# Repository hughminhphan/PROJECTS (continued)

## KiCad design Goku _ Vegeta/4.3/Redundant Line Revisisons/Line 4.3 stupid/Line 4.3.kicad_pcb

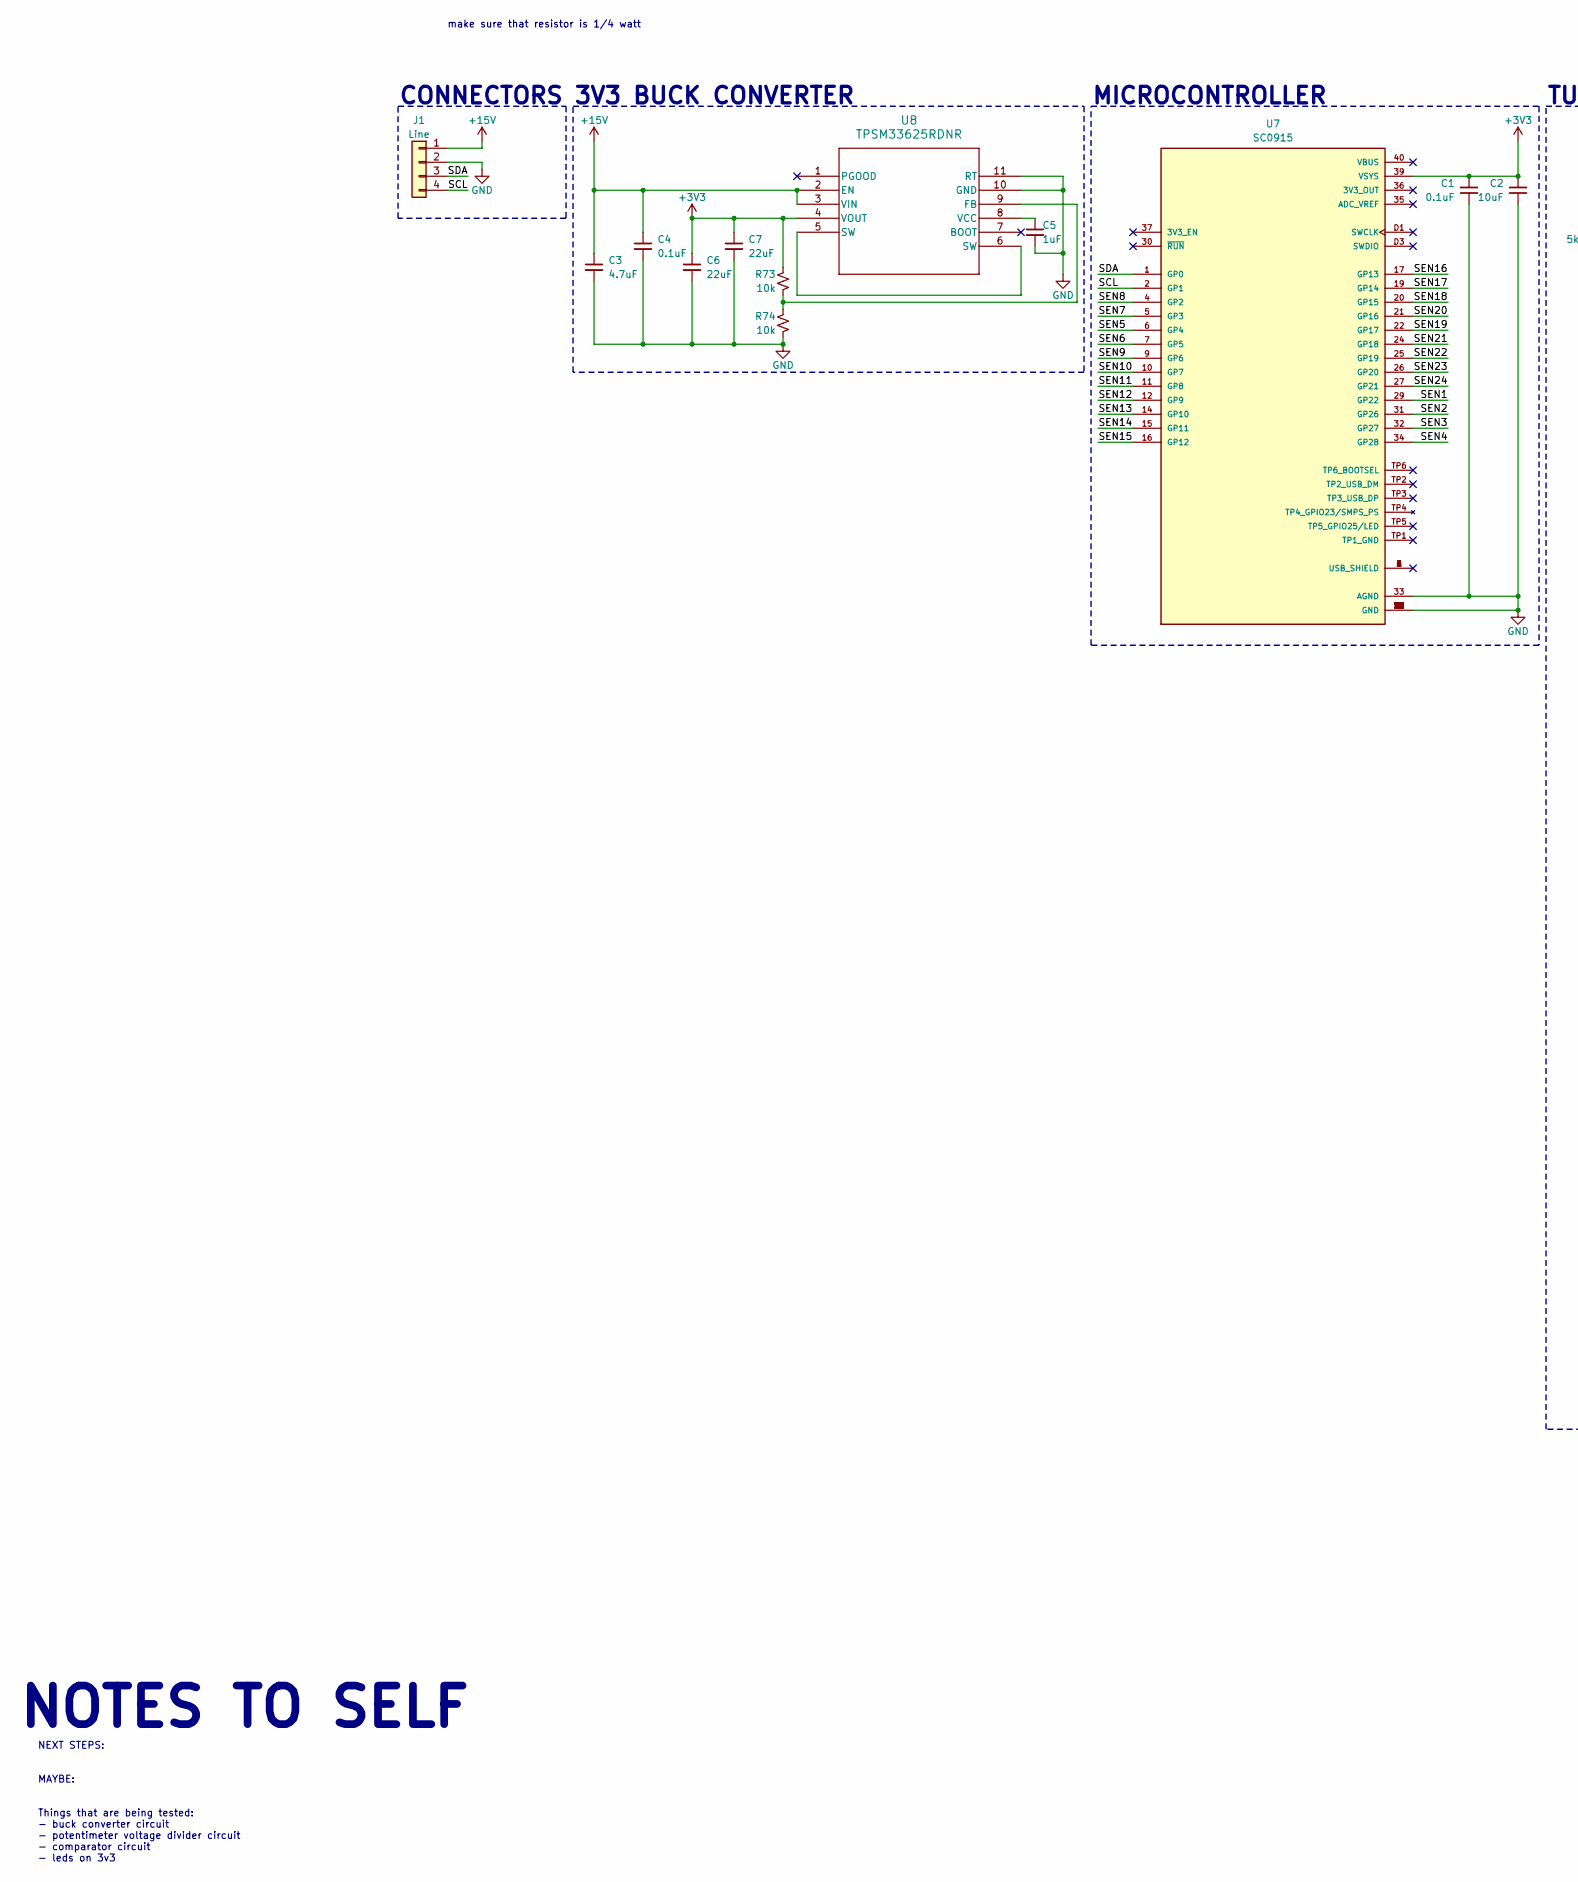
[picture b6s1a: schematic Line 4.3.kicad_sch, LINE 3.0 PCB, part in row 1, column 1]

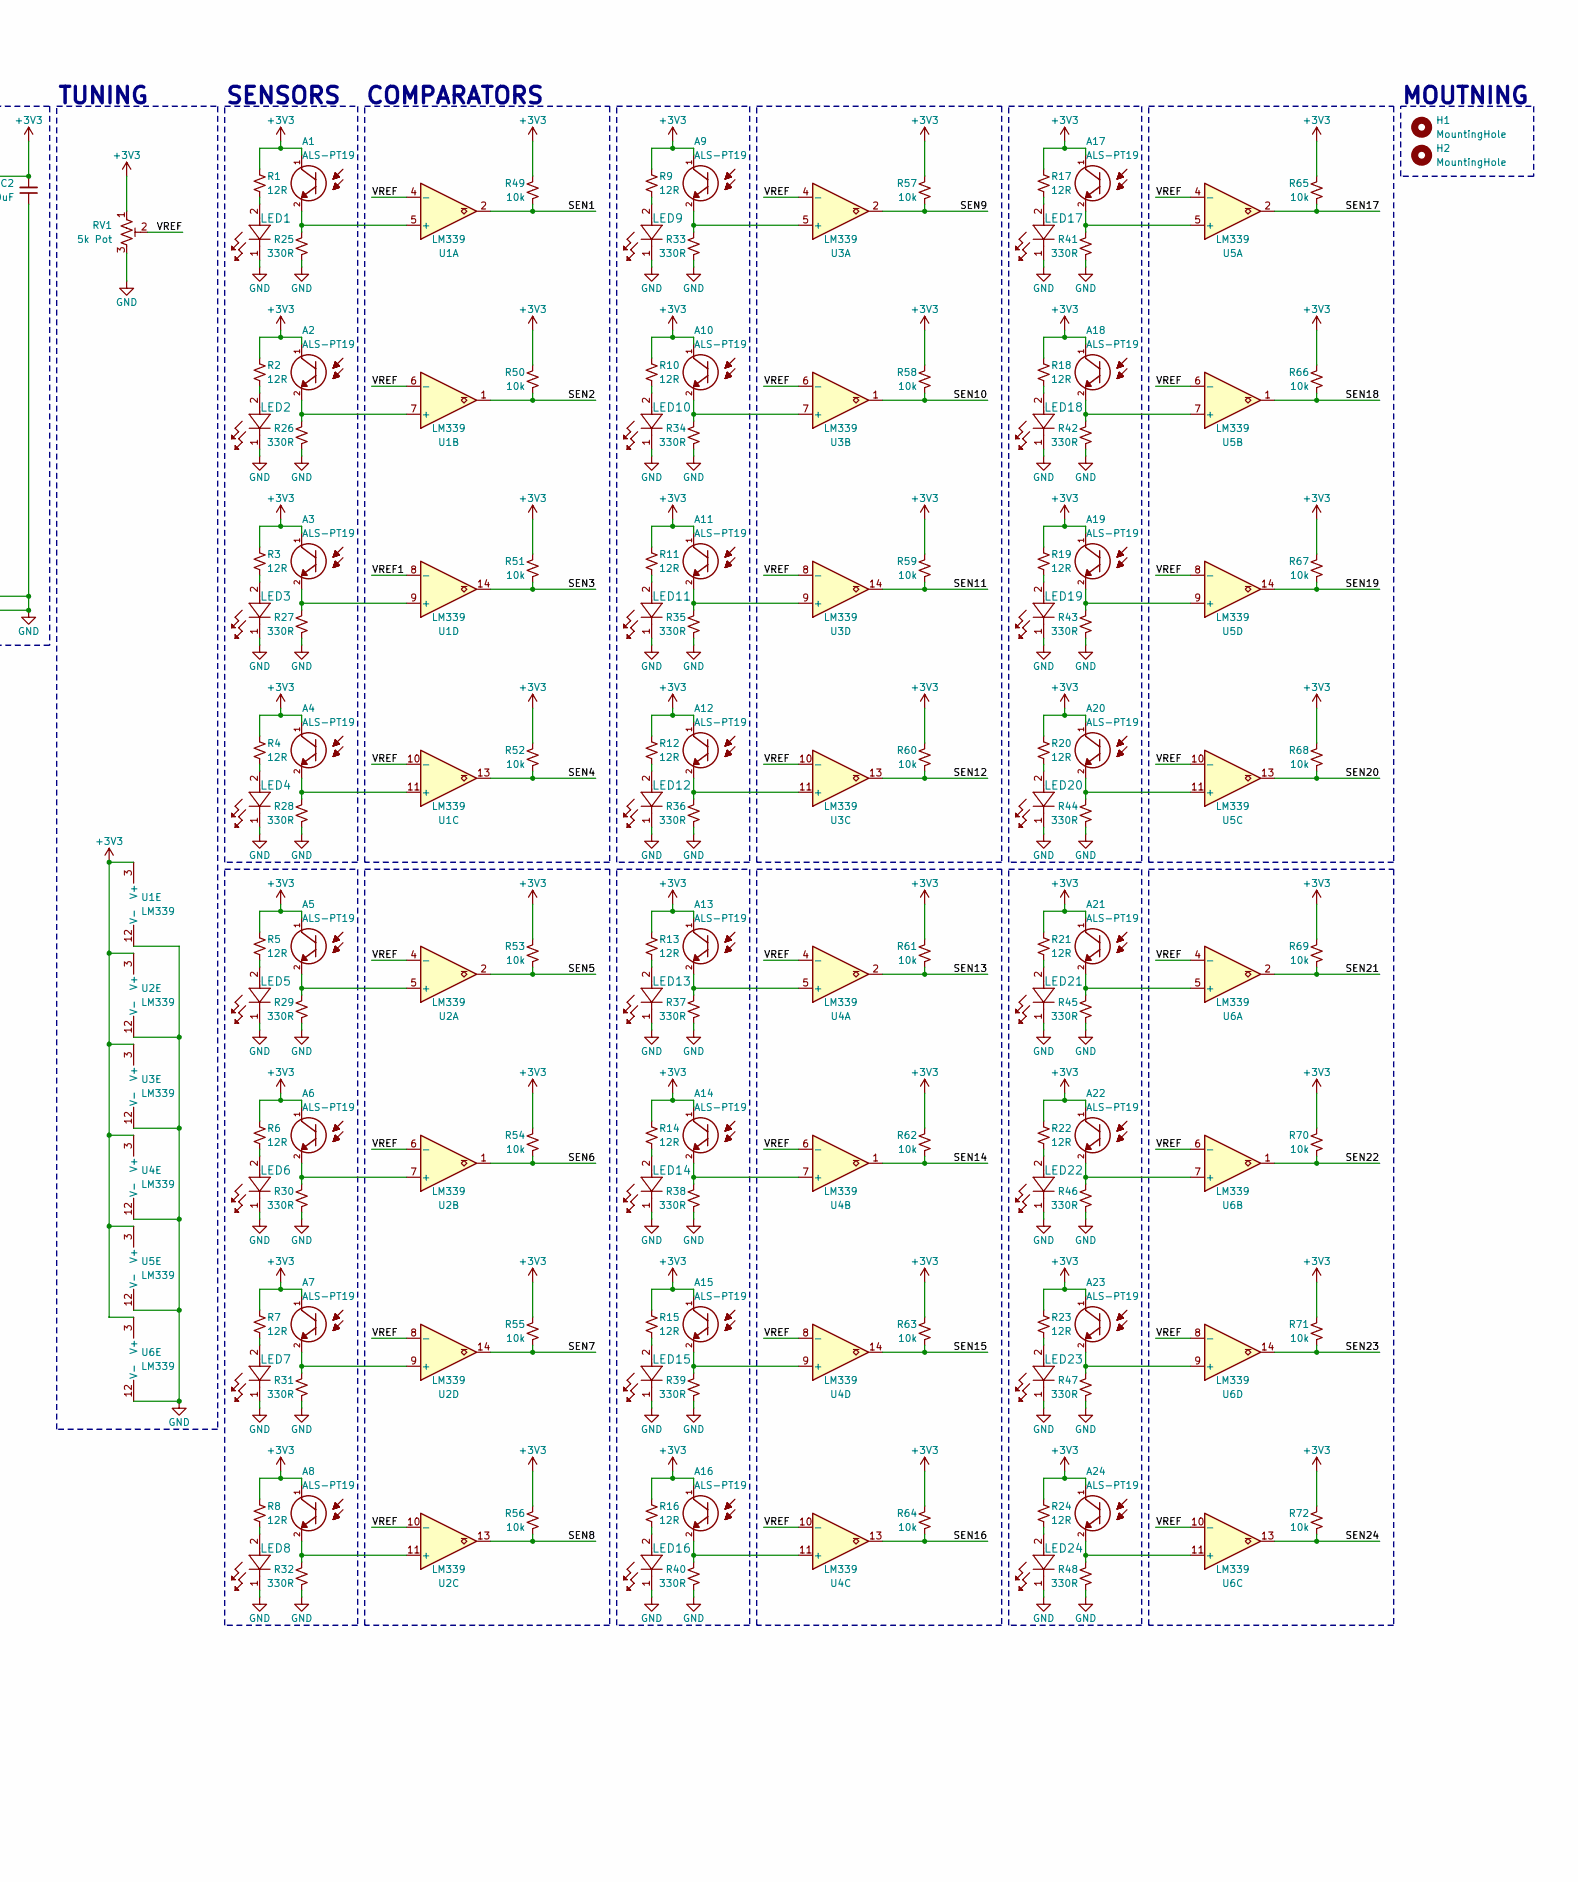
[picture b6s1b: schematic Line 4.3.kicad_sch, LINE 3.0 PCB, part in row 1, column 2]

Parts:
A1: ALS-PT19; R_1210_3225Metric; PARTREV 5
A2, A3, A4, A5, A6, A7, A8, A9, A10, A11, A12, A13, A14, A15, A16, A17, A18, A19, A20, A21, A22, A23, A24: ALS-PT19; XDCR_ALS-PT19-315C_L177_TR8; PARTREV 5
C1: 0.1uF; C_0402_1005Metric
C2: 10uF; 0805
C3: 4.7uF; C_0805_2012Metric
C4: 0.1uF; C_0805_2012Metric
C5: 1uF; C_0805_2012Metric
C6, C7: 22uF; C_0805_2012Metric
H1, H2: MountingHole; MountingHole_3.2mm_M3
J1: Line; JST_XH_B4B-XH-A_1x04_P2.50mm_Vertical
LED1, LED2, LED3, LED4, LED5, LED6, LED7, LED8, LED9, LED10, LED11, LED12, LED13, LED14, LED15, LED16, LED17, LED18, LED19, LED20, LED21, LED22, LED23, LED24: JB2835AWT-W-U30GA0000-N0000001; LED_J2835_CRW
R1, R2, R3, R4, R5, R6, R7, R8, R9, R10, R11, R12, R13, R14, R15, R16, R17, R18, R19, R20, R21, R22, R23, R24: 12R; 0805
R25, R26, R27, R28, R29, R30, R31, R32, R33, R34, R35, R36, R37, R38, R39, R40, R41, R42, R43, R44, R45, R46, R47, R48: 330R; 0805
R49, R50, R51, R52, R53, R54, R55, R56, R57, R58, R59, R60, R61, R62, R63, R64, R65, R66, R67, R68, R69, R70, R71, R72, R73, R74: 10k; 0805
RV1: 5k Pot; Potentiometer_Piher_PT-10-V10_Vertical
U1, U2, U3, U4, U5, U6: LM339; TSSOP-14_W4.4mm
U7: SC0915; MODULE_SC0915; PARTREV 1.9
U8: TPSM33625RDNR; QFN-FCMOD11_RDN_TEX

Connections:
+3V3: A1.1, A2.1, A3.1, A4.1, A5.1, A6.1, A7.1, A8.1, A9.1, A10.1, A11.1, A12.1, A13.1, A14.1, A15.1, A16.1, A17.1, A18.1, A19.1, A20.1, A21.1, A22.1, A23.1, A24.1, C1.2, C2.2, C6.1, C7.1, R1.1, R2.1, R3.1, R4.1, R5.1, R6.1, R7.1, R8.1, R9.1, R10.1, R11.1, R12.1, R13.1, R14.1, R15.1, R16.1, R17.1, R18.1, R19.1, R20.1, R21.1, R22.1, R23.1, R24.1, R49.2, R50.2, R51.2, R52.2, R53.2, R54.2, R55.2, R56.2, R57.2, R58.2, R59.2, R60.2, R61.2, R62.2, R63.2, R64.2, R65.2, R66.2, R67.2, R68.2, R69.2, R70.2, R71.2, R72.2, R73.2, RV1.1, U1.3 (V+), U2.3 (V+), U3.3 (V+), U4.3 (V+), U5.3 (V+), U6.3 (V+), U7.39 (VSYS), U8.4 (VOUT)
+15V: C3.1, C4.1, J1.1, U8.2 (EN), U8.3 (VIN)
/SCL: J1.4, U7.2 (GP1)
/SDA: J1.3, U7.1 (GP0)
/SEN1: R49.1, U1.2, U7.29 (GP22)
/SEN2: R50.1, U1.1, U7.31 (GP26)
/SEN3: R51.1, U1.14, U7.32 (GP27)
/SEN4: R52.1, U1.13, U7.34 (GP28)
/SEN5: R53.1, U2.2, U7.6 (GP4)
/SEN6: R54.1, U2.1, U7.7 (GP5)
/SEN7: R55.1, U2.14, U7.5 (GP3)
/SEN8: R56.1, U2.13, U7.4 (GP2)
/SEN9: R57.1, U3.2, U7.9 (GP6)
/SEN10: R58.1, U3.1, U7.10 (GP7)
/SEN11: R59.1, U3.14, U7.11 (GP8)
/SEN12: R60.1, U3.13, U7.12 (GP9)
/SEN13: R61.1, U4.2, U7.14 (GP10)
/SEN14: R62.1, U4.1, U7.15 (GP11)
/SEN15: R63.1, U4.14, U7.16 (GP12)
/SEN16: R64.1, U4.13, U7.17 (GP13)
/SEN17: R65.1, U5.2, U7.19 (GP14)
/SEN18: R66.1, U5.1, U7.20 (GP15)
/SEN19: R67.1, U5.14, U7.22 (GP17)
/SEN20: R68.1, U5.13, U7.21 (GP16)
/SEN21: R69.1, U6.2, U7.24 (GP18)
/SEN22: R70.1, U6.1, U7.25 (GP19)
/SEN23: R71.1, U6.14, U7.26 (GP20)
/SEN24: R72.1, U6.13, U7.27 (GP21)
/VREF: RV1.2, U1.4 (-), U1.6 (-), U1.10 (-), U2.4 (-), U2.6 (-), U2.8 (-), U2.10 (-), U3.4 (-), U3.6 (-), U3.8 (-), U3.10 (-), U4.4 (-), U4.6 (-), U4.8 (-), U4.10 (-), U5.4 (-), U5.6 (-), U5.8 (-), U5.10 (-), U6.4 (-), U6.6 (-), U6.8 (-), U6.10 (-)
/VREF1: U1.8 (-)
GND: C1.1, C2.1, C3.2, C4.2, C5.2, C6.2, C7.2, J1.2, LED1.1, LED2.1, LED3.1, LED4.1, LED5.1, LED6.1, LED7.1, LED8.1, LED9.1, LED10.1, LED11.1, LED12.1, LED13.1, LED14.1, LED15.1, LED16.1, LED17.1, LED18.1, LED19.1, LED20.1, LED21.1, LED22.1, LED23.1, LED24.1, R25.1, R26.1, R27.1, R28.1, R29.1, R30.1, R31.1, R32.1, R33.1, R34.1, R35.1, R36.1, R37.1, R38.1, R39.1, R40.1, R41.1, R42.1, R43.1, R44.1, R45.1, R46.1, R47.1, R48.1, R74.1, RV1.3, U1.12 (V-), U2.12 (V-), U3.12 (V-), U4.12 (V-), U5.12 (V-), U6.12 (V-), U7.3 (GND), U7.8 (GND), U7.13 (GND), U7.18 (GND), U7.23 (GND), U7.28 (GND), U7.33 (AGND), U7.38 (GND), U7.D2 (GND), U8.10 (GND), U8.11 (RT)
unnamed: LED1.2, R1.2
unnamed: LED2.2, R2.2
unnamed: LED3.2, R3.2
unnamed: LED4.2, R4.2
unnamed: LED5.2, R5.2
unnamed: LED6.2, R6.2
unnamed: LED7.2, R7.2
unnamed: LED8.2, R8.2
unnamed: LED9.2, R9.2
unnamed: LED10.2, R10.2
unnamed: LED11.2, R11.2
unnamed: LED12.2, R12.2
unnamed: LED13.2, R13.2
unnamed: LED14.2, R14.2
unnamed: LED15.2, R15.2
unnamed: LED16.2, R16.2
unnamed: LED17.2, R17.2
unnamed: LED18.2, R18.2
unnamed: LED19.2, R19.2
unnamed: LED20.2, R20.2
unnamed: LED21.2, R21.2
unnamed: LED22.2, R22.2
unnamed: LED23.2, R23.2
unnamed: LED24.2, R24.2
unnamed: A1.2, R25.2, U1.5 (+)
unnamed: A2.2, R26.2, U1.7 (+)
unnamed: A4.2, R28.2, U1.11 (+)
unnamed: A3.2, R27.2, U1.9 (+)
unnamed: A5.2, R29.2, U2.5 (+)
unnamed: A6.2, R30.2, U2.7 (+)
unnamed: A8.2, R32.2, U2.11 (+)
unnamed: A7.2, R31.2, U2.9 (+)
unnamed: A9.2, R33.2, U3.5 (+)
unnamed: A10.2, R34.2, U3.7 (+)
unnamed: A12.2, R36.2, U3.11 (+)
unnamed: A11.2, R35.2, U3.9 (+)
unnamed: A13.2, R37.2, U4.5 (+)
unnamed: A14.2, R38.2, U4.7 (+)
unnamed: A16.2, R40.2, U4.11 (+)
unnamed: A15.2, R39.2, U4.9 (+)
unnamed: A17.2, R41.2, U5.5 (+)
unnamed: A18.2, R42.2, U5.7 (+)
unnamed: A20.2, R44.2, U5.11 (+)
unnamed: A19.2, R43.2, U5.9 (+)
unnamed: A21.2, R45.2, U6.5 (+)
unnamed: A22.2, R46.2, U6.7 (+)
unnamed: A24.2, R48.2, U6.11 (+)
unnamed: A23.2, R47.2, U6.9 (+)
unnamed: R73.1, R74.2, U8.9 (FB)
unnamed: U8.5 (SW), U8.6 (SW)
unnamed: C5.1, U8.8 (VCC)

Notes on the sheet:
NOTES TO SELF
NEXT STEPS: MAYBE: Things that are being tested: - buck converter circuit - potentimeter voltage divider circuit - comparator circuit - leds on 3v3
MOUTNING
SENSORS
TUNING
make sure that resistor is 1/4 watt
CONNECTORS
3V3 BUCK CONVERTER
MICROCONTROLLER
COMPARATORS

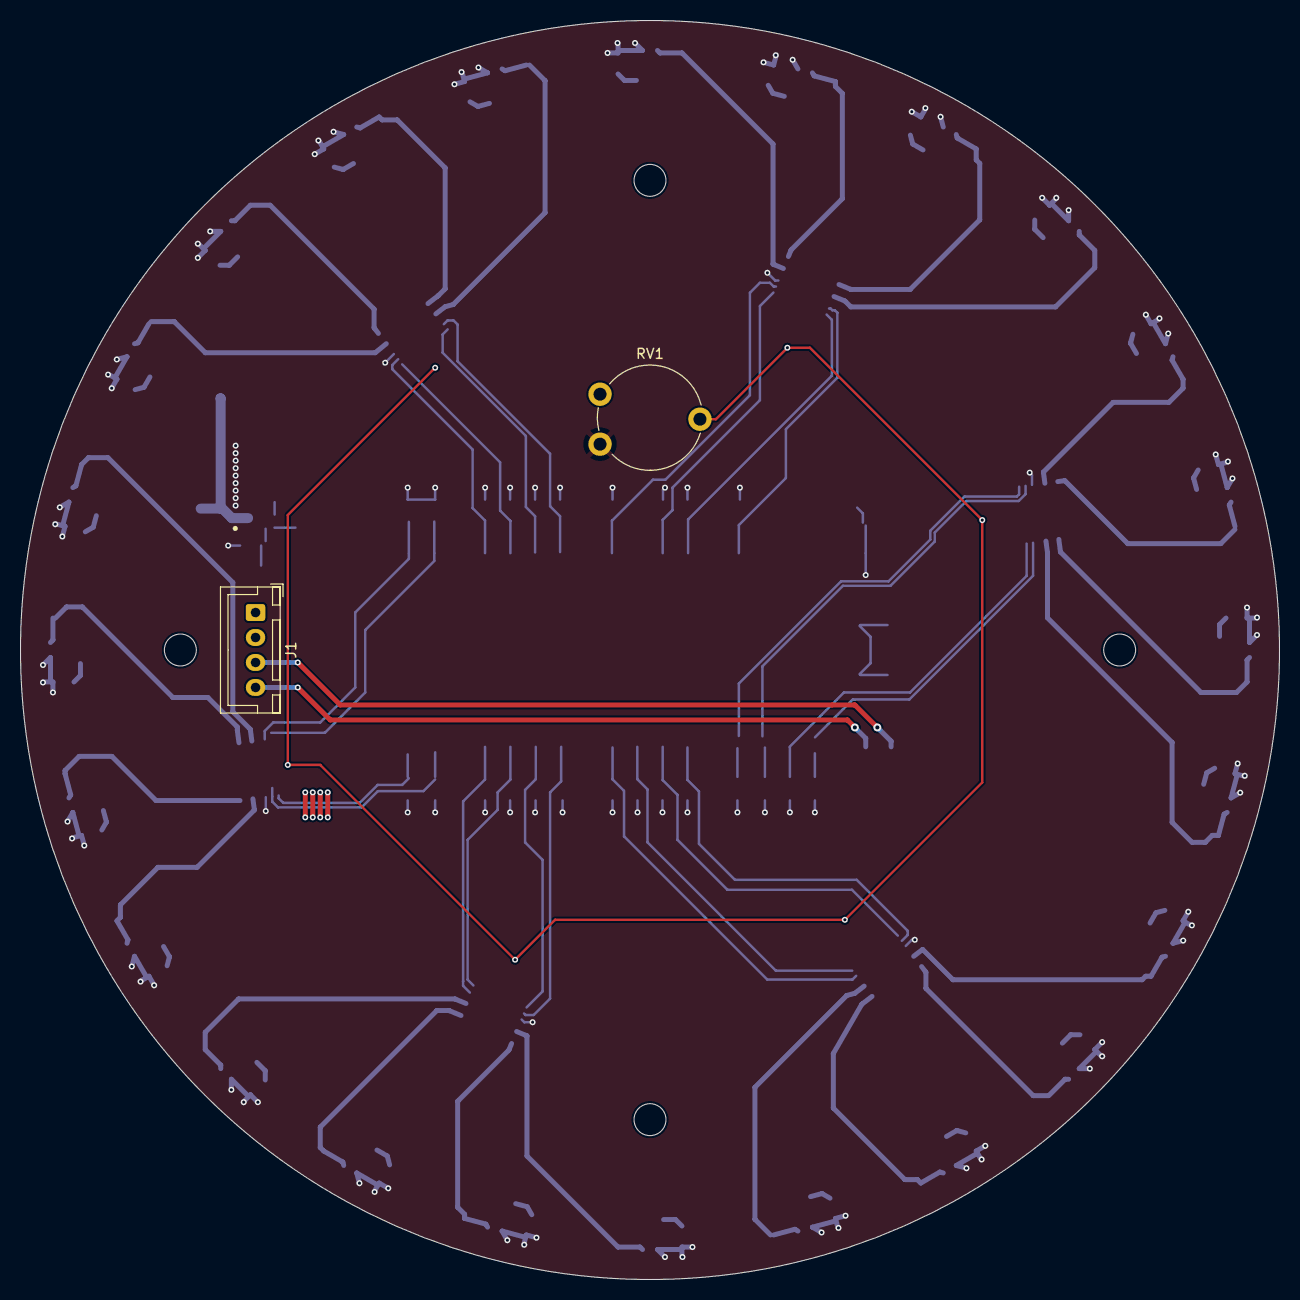
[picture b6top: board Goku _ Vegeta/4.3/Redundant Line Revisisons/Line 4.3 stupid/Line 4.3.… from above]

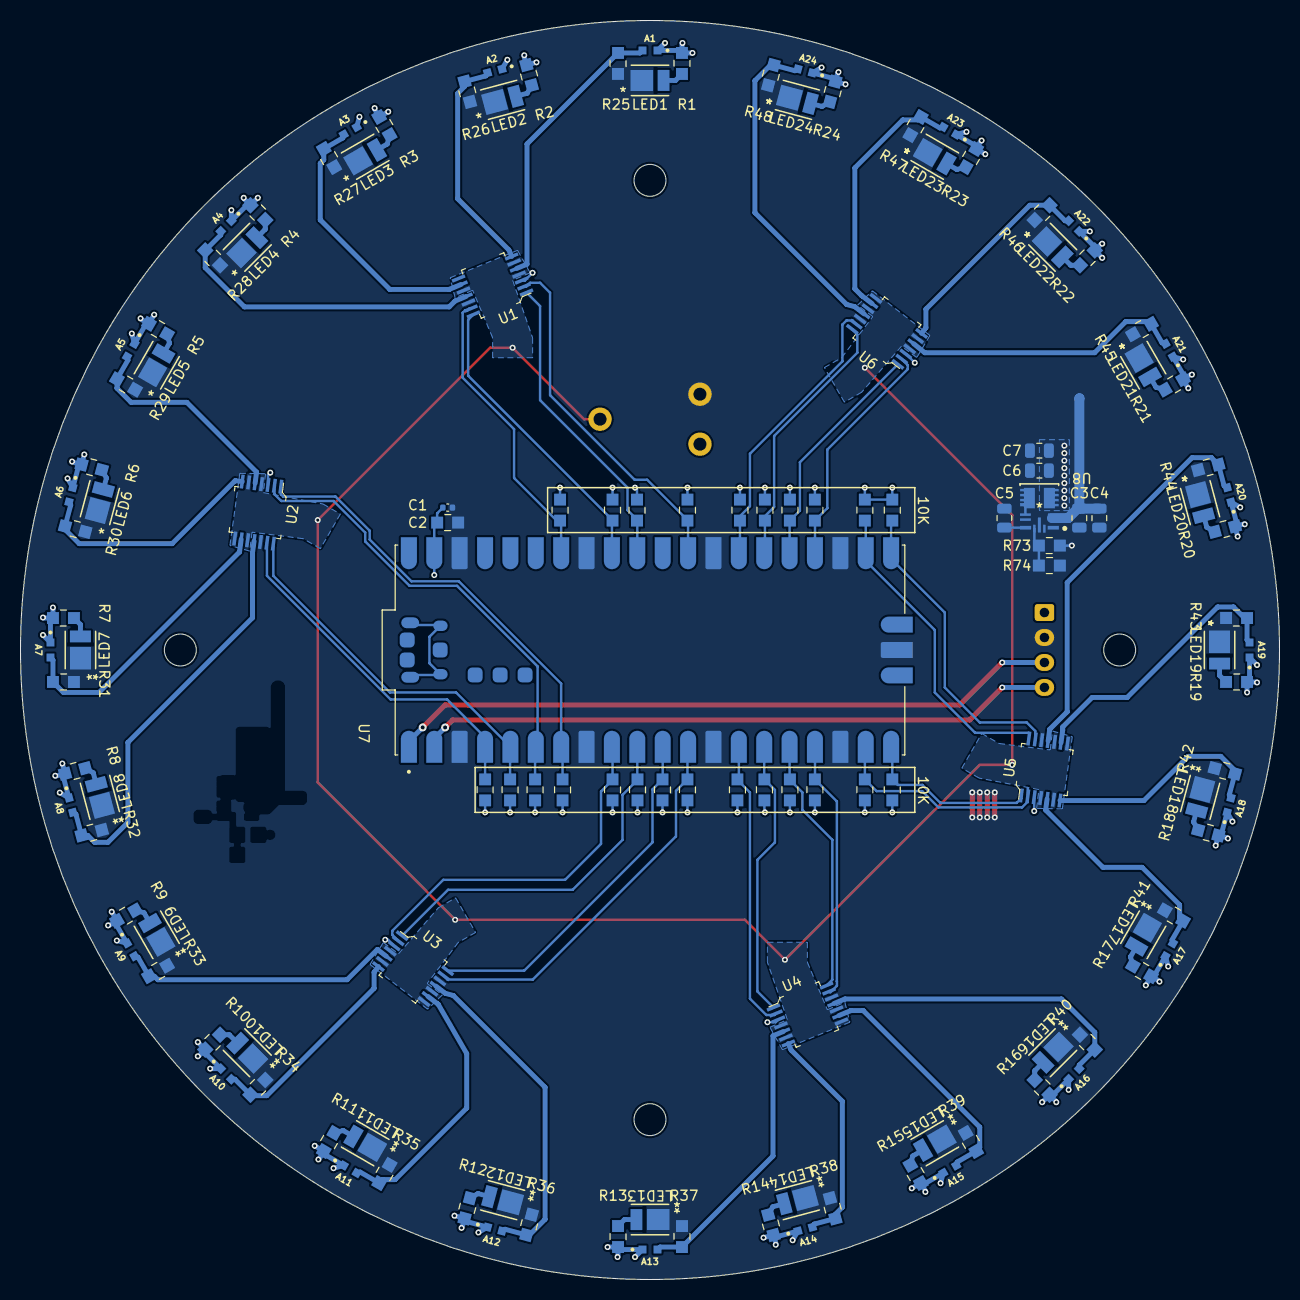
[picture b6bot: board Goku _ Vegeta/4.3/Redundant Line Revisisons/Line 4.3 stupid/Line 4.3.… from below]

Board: 2 copper layers, 126.0 x 126.0 mm, 143 parts (137 on the bottom side), 81 nets.

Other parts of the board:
H3, H4: MountingHole; MountingHole_3.2mm_M3
